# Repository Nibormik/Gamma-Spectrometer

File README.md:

# Gamma-Spectrometer
This is a Compact Gammaspectrometer Based On the Scematics and component choise of the [Open-Gamma-Detector](https://github.com/Open-Gamma-Project/Open-Gamma-Detector).
Its only Designed for testing purposes and should never be used in a production enviorment.  
<br>
This version of the Gamma spectrometer was designed with a few strict restrictions in mind.

#### Restrictions
<br>
The main rrestrictions:  <br>

- Power
    - <= 50ma
    - 5v
    - low noise
- physical limitations
    - pcb
        - width 50mm
        - height 30 mm
    - rocket interior diameter 98mm
        - max center height from pcb 38 mm
        - max edge height from pcb 28 mm 
- comunication
    - analog rocket input
        - update frequencey 2000hz - 4000hz
        - 8 bit resolution
    - digital input
        - 8bit digital paralell
        - estimated update frequency 20hz

## Similarities between projects

Since this is based upon the schematic of the Open Gamma Detector there are not allot of diffrences.  
Main diffrences are a diffrent cpu and the data output (wich is stricly analog)
Due to the enviorment, to-way comunictation is not possible so the bord does not support it.

The scintilator end general operational methon of the systen is equal to that of the Opgen Gamma Detector

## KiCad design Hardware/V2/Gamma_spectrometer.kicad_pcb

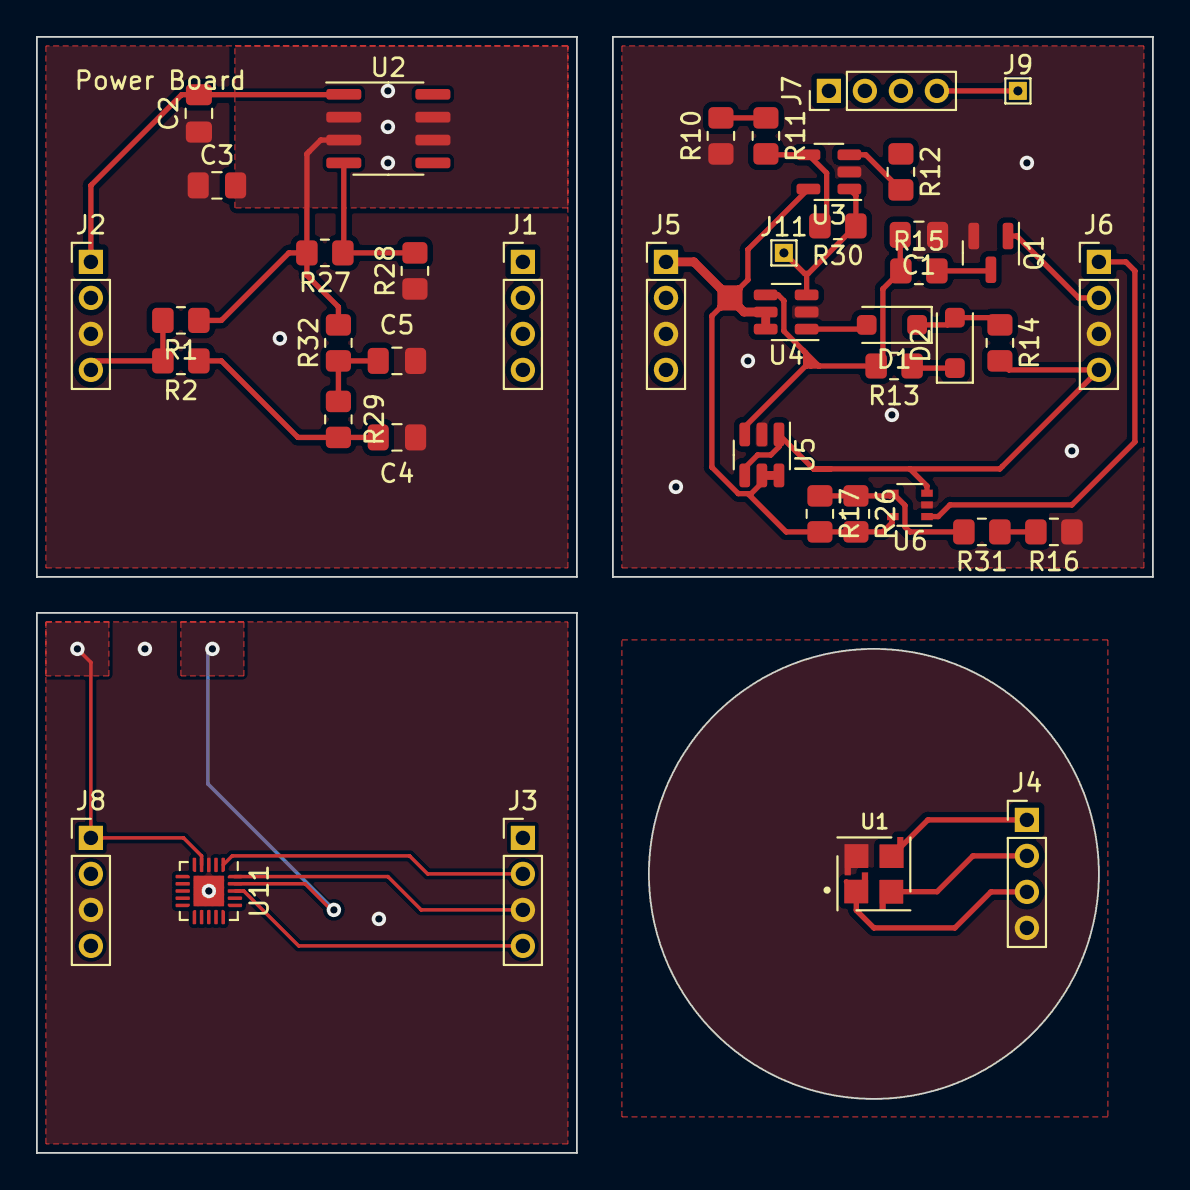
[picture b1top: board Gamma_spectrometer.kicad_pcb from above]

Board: 2 copper layers, 62.0 x 62.0 mm, 42 parts (0 on the bottom side), 32 nets.

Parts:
C1, C2, C3: C; C_0805_2012Metric_Pad1.18x1.45mm_HandSolder
C4, C5: 10n; C_0805_2012Metric_Pad1.18x1.45mm_HandSolder
D1, D2: PMEG6010CEH; D_SOD-123F
J1, J2, J3, J4, J5, J6, J7, J8: Conn_01x04; PinHeader_1x04_P2.00mm_Vertical
J9, J11: Test Pad; TestPoint_THTPad_1.0x1.0mm_Drill0.5mm
Q1: 2N7002; SOT-23
R1, R2: 0; R_0805_2012Metric_Pad1.20x1.40mm_HandSolder
R10, R11: 10; R_0805_2012Metric_Pad1.20x1.40mm_HandSolder
R12, R13, R29, R32: 49.9; R_0805_2012Metric_Pad1.20x1.40mm_HandSolder
R14, R15, R16: 1000; R_0805_2012Metric_Pad1.20x1.40mm_HandSolder
R17, R26: 107K; R_0805_2012Metric_Pad1.20x1.40mm_HandSolder
R27, R28, R30, R31: ?; R_0805_2012Metric_Pad1.20x1.40mm_HandSolder
U1: MICROFC-30035-SMT-TR1; XDCR_MICROFC-30035-SMT-TR1
U2: LM317L_SO8; SOIC-8_3.9x4.9mm_P1.27mm
U3: OPA356xxDBV; SOT-23-5
U4, U5: OPA357AIDVBR; SOT-23-6
U6: LMV7219M7; SOT-353_SC-70-5
U11: ATtiny1616-M; VQFN-20-1EP_3x3mm_P0.4mm_EP1.7x1.7mm

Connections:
+5V: J5.1, J8.1, R17.2, R26.2, U3.5 (V+), U4.5 (ENABLE), U4.6 (V+), U5.5 (ENABLE), U5.6 (V+), U6.5 (V+), U11.4 (VCC)
GND: C1.1, J5.3, J6.3, Q1.2 (S), R10.1, R16.1, U3.2 (V-), U4.2 (V-), U5.2 (V-), U6.2 (V-)
GND1: J4.4, U1.4
GND2: C2.1, C3.1, C4.2, C5.2, J2.3, R28.1
GND3: J3.3, J8.3, U11.3 (GND), U11.21 (GND)
INT: J6.1, U6.1
unnamed: C3.2, R1.1, R27.2, R32.2, U2.2 (VO), U2.3 (VO), U2.6 (VO), U2.7 (VO)
unnamed: C4.1, R2.1, R29.1
unnamed: C5.1, R29.2, R32.1
unnamed: D1.2 (A), U4.1
unnamed: D1.1 (K), D2.2 (A), R14.1
unnamed: D2.1 (K), R13.1
unnamed: C2.2, J2.1, U2.1 (VI)
unnamed: J2.4, R1.2, R2.2
unnamed: J3.1, U11.1 (PA2)
unnamed: J3.2, U11.20 (PA1)
unnamed: J3.4, U11.18 (PC3)
unnamed: J4.1, U1.3
unnamed: J4.2, U1.2
unnamed: J4.3, U1.1
unnamed: J11.1, R30.1, U3.1, U4.3 (+)
unnamed: Q1.3 (D), R15.2
unnamed: R10.2, R11.1
unnamed: R16.2, R31.1
unnamed: R27.1, R28.2, U2.4 (ADJ)
unnamed: R12.2, U3.3 (+)
unnamed: R11.2, R30.2, U3.4 (-)
unnamed: C1.2, R13.2, R15.1, U4.4 (-), U5.3 (+)
unnamed: R17.1, R26.1, R31.2, U6.4 (-)
Reset: J6.2, Q1.1 (G)
SIPM: J7.1, J7.2, J7.3, J7.4, J9.1, R12.1
Signal: J6.4, R14.2, U5.1, U5.4 (-), U6.3 (+)

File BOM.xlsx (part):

Column1 | Column2 | Column3 | Column4 | Column5 | Column6 | Column7 | Column8 | Column9 | Column10 | Column11
Source: | C:\Users\Nibne\Documents\Gamma Spectrometer\Hardware\Gamma_spectrometer.kicad_s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
Date: | 2/6/2023 2:52:58 PM
Tool: | Eeschema (6.0.8)
Generator: | C:\Program Files\KiCad\6.0\bin\scripting\plugins/bom_csv_grouped_by_value.py
Component Count: | 47
Individual Components:
Item | Qty | Reference(s) | Value | LibPart | Footprint | Datasheet | MANUFACTURER | MAXIMUM_PACKAGE_HEIGHT | PARTREV | STANDARD
 |  | C1 | C | Device:C | Capacitor_SMD:C_0805_2012Metric_Pad1.18x1.45mm_HandSolder | ~
 |  | C2 | C | Device:C | Capacitor_SMD:C_0805_2012Metric_Pad1.18x1.45mm_HandSolder | ~
 |  | C3 | C | Device:C | Capacitor_SMD:C_0805_2012Metric_Pad1.18x1.45mm_HandSolder | ~
 |  | C4 | 10n | Device:C | Capacitor_SMD:C_0805_2012Metric_Pad1.18x1.45mm_HandSolder | ~
 |  | C5 | 10n | Device:C | Capacitor_SMD:C_0805_2012Metric_Pad1.18x1.45mm_HandSolder | ~
 |  | D1 | PMEG6010CEH | Diode:PMEG6010CEH | Diode_SMD:D_SOD-123F | https://assets.nexperia.com/documents/data-sheet/PMEG6010CEH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
 |  | D2 | PMEG6010CEH | Diode:PMEG6010CEH | Diode_SMD:D_SOD-123F | https://assets.nexperia.com/documents/data-sheet/PMEG6010CEH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
 |  | J1 | Conn_01x04 | Connector_Generic:Conn_01x04 | Connector_PinHeader_2.00mm:PinHeader_1x04_P2.00mm_Vertical | ~
 |  | J2 | Conn_01x04 | Connector_Generic:Conn_01x04 | Connector_PinHeader_2.00mm:PinHeader_1x04_P2.00mm_Vertical | ~
 |  | J3 | Conn_01x01 | Connector_Generic:Conn_01x01 | Connector_PinHeader_2.00mm:PinHeader_1x01_P2.00mm_Vertical | ~
 |  | J4 | Conn_01x04 | Connector_Generic:Conn_01x04 | Connector_PinHeader_2.00mm:PinHeader_1x04_P2.00mm_Vertical | ~
 |  | J5 | Test Pad | Connector:Conn_01x01_Female | TestPoint:TestPoint_THTPad_1.0x1.0mm_Drill0.5mm | ~
 |  | J6 | Test Pad | Connector:Conn_01x01_Female | TestPoint:TestPoint_THTPad_1.0x1.0mm_Drill0.5mm | ~
 |  | J7 | Test Pad | Connector:Conn_01x01_Female | TestPoint:TestPoint_THTPad_1.0x1.0mm_Drill0.5mm | ~
 |  | J8 | Test Pad | Connector:Conn_01x01_Female | TestPoint:TestPoint_THTPad_1.0x1.0mm_Drill0.5mm | ~
 |  | J9 | Test Pad | Connector:Conn_01x01_Female | TestPoint:TestPoint_THTPad_1.0x1.0mm_Drill0.5mm | ~
 |  | J10 | Test Pad | Connector:Conn_01x01_Female | TestPoint:TestPoint_THTPad_1.0x1.0mm_Drill0.5mm | ~
 |  | J11 | Test Pad | Connector:Conn_01x01_Female | TestPoint:TestPoint_THTPad_1.0x1.0mm_Drill0.5mm | ~
 |  | J12 | Test Pad | Connector:Conn_01x01_Female | TestPoint:TestPoint_THTPad_1.0x1.0mm_Drill0.5mm | ~
 |  | Q1 | 2N7002 | Transistor_FET:2N7002 | Package_TO_SOT_SMD:SOT-23 | https://www.onsemi.com/pub/Collateral/NDS7002A-D.PDF
 |  | R1 | 49.9 | Device:R | Resistor_SMD:R_0805_2012Metric_Pad1.20x1.40mm_HandSolder | ~
 |  | R10 | 10 | Device:R | Resistor_SMD:R_0805_2012Metric_Pad1.20x1.40mm_HandSolder | ~
 |  | R11 | 10 | Device:R | Resistor_SMD:R_0805_2012Metric_Pad1.20x1.40mm_HandSolder | ~
 |  | R12 | 49.9 | Device:R | Resistor_SMD:R_0805_2012Metric_Pad1.20x1.40mm_HandSolder | ~
 |  | R13 | 49.9 | Device:R | Resistor_SMD:R_0805_2012Metric_Pad1.20x1.40mm_HandSolder | ~
 |  | R14 | 1000 | Device:R | Resistor_SMD:R_0805_2012Metric_Pad1.20x1.40mm_HandSolder | ~
 |  | R15 | 1000 | Device:R | Resistor_SMD:R_0805_2012Metric_Pad1.20x1.40mm_HandSolder | ~
 |  | R16 | 1000 | Device:R | Resistor_SMD:R_0805_2012Metric_Pad1.20x1.40mm_HandSolder | ~
 |  | R17 | 107K | Device:R | Resistor_SMD:R_0805_2012Metric_Pad1.20x1.40mm_HandSolder | ~
 |  | R26 | 107K | Device:R | Resistor_SMD:R_0805_2012Metric_Pad1.20x1.40mm_HandSolder | ~
 |  | R27 | ? | Device:R | Resistor_SMD:R_0805_2012Metric_Pad1.20x1.40mm_HandSolder | ~
 |  | R28 | ? | Device:R | Resistor_SMD:R_0805_2012Metric_Pad1.20x1.40mm_HandSolder | ~
 |  | R29 | 49.9 | Device:R | Resistor_SMD:R_0805_2012Metric_Pad1.20x1.40mm_HandSolder | ~
 |  | R30 | ? | Device:R | Resistor_SMD:R_0805_2012Metric_Pad1.20x1.40mm_HandSolder | ~
 |  | R31 | ? | Device:R | Resistor_SMD:R_0805_2012Metric_Pad1.20x1.40mm_HandSolder | ~
 |  | R32 | 49.9 | Device:R | Resistor_SMD:R_0805_2012Metric_Pad1.20x1.40mm_HandSolder | ~
 |  | R33 | 1000 | Device:R | Resistor_SMD:R_0805_2012Metric_Pad1.20x1.40mm_HandSolder | ~
 |  | R34 | 1000 | Device:R | Resistor_SMD:R_0805_2012Metric_Pad1.20x1.40mm_HandSolder | ~
 |  | SIPM1 | MICROFC-30035-SMT-TR1 | MICROFC-30035-SMT-TR1:MICROFC-30035-SMT-TR1 | MICROFC-30035-SMT-TR1:XDCR_MICROFC-30035-SMT-TR1 |  | On Semiconductor | 0.70 mm | Issue O | Manufacturer Recommendations
 |  | U2 | LM317L_SO8 | Regulator_Linear:LM317L_SO8 | Package_SO:SOIC-8_3.9x4.9mm_P1.27mm | http://www.ti.com/lit/ds/snvs775k/snvs775k.pdf
 |  | U3 | OPA356xxDBV | Amplifier_Operational:OPA356xxDBV | Package_TO_SOT_SMD:SOT-23-5 | http://www.ti.com/lit/ds/symlink/opa356.pdf
 |  | U4 | OPA357AIDVBR | Amplifier_Operational:OPA355NA | Package_TO_SOT_SMD:SOT-23-6 | http://www.ti.com/lit/ds/symlink/opa355.pdf
 |  | U5 | OPA357AIDVBR | Amplifier_Operational:OPA355NA | Package_TO_SOT_SMD:SOT-23-6 | http://www.ti.com/lit/ds/symlink/opa355.pdf
 |  | U6 | LMV7219M7 | Comparator:LMV7219M7 | Package_TO_SOT_SMD:SOT-353_SC-70-5 | https://www.ti.com/lit/ds/symlink/lmv7219.pdf
 |  | U7 | OPA356xxDBV | Amplifier_Operational:OPA356xxDBV | Package_TO_SOT_SMD:SOT-23-5 | http://www.ti.com/lit/ds/symlink/opa356.pdf
 |  | U8 | FODM217A | Isolator:FODM217A | Package_SO:SOP-4_4.4x2.6mm_P1.27mm | https://www.onsemi.com/pub/Collateral/FODM214-D.PDF
 |  | U11 | ATtiny1616-M | MCU_Microchip_ATtiny:ATtiny1616-M | Package_DFN_QFN:VQFN-20-1EP_3x3mm_P0.4mm_EP1.7x1.7mm | http://ww1.microchip.com/downloads/en/DeviceDoc/ATtiny3216_A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
Collated Components:
Item | Qty | Reference(s) | Value | LibPart | Footprint | Datasheet | MANUFACTURER | MAXIMUM_PACKAGE_HEIGHT | PARTREV | STANDARD
1 | 3 | C1, C2, C3 | C |  | Capacitor_SMD:C_0805_2012Metric_Pad1.18x1.45mm_HandSolder | ~
2 | 2 | C4, C5 | 10n |  | Capacitor_SMD:C_0805_2012Metric_Pad1.18x1.45mm_HandSolder | ~
3 | 2 | D1, D2 | PMEG6010CEH | Kan Erstates Med lignende Komponenter | Diode_SMD:D_SOD-123F | https://assets.nexperia.com/documents/data-sheet/PMEG6010CEH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
4 | 3 | J1, J2, J4 | Conn_01x04 | 1stk Rakett konnector 2stk pin header | Connector_PinHeader_2.00mm:PinHeader_1x04_P2.00mm_Vertical | ~
5 | 1 | J3 | Conn_01x01 | rakett CLK konnector | Connector_PinHeader_2.00mm:PinHeader_1x01_P2.00mm_Vertical | ~
6 | 8 | J5, J6, J7, J8, J9, J10, J11, J12 | Test Pad |  | TestPoint:TestPoint_THTPad_1.0x1.0mm_Drill0.5mm | ~
7 | 1 | Q1 | 2N7002 | Kan Erstates Med lignende Komponenter | Package_TO_SOT_SMD:SOT-23 | https://www.onsemi.com/pub/Collateral/NDS7002A-D.PDF
8 | 5 | R1, R12, R13, R29, R32 | 49.9 |  | Resistor_SMD:R_0805_2012Metric_Pad1.20x1.40mm_HandSolder | ~
9 | 2 | R10, R11 | 10 |  | Resistor_SMD:R_0805_2012Metric_Pad1.20x1.40mm_HandSolder | ~
10 | 5 | R14, R15, R16, R33, R34 | 1000 |  | Resistor_SMD:R_0805_2012Metric_Pad1.20x1.40mm_HandSolder | ~
11 | 2 | R17, R26 | 107K |  | Resistor_SMD:R_0805_2012Metric_Pad1.20x1.40mm_HandSolder | ~
12 | 4 | R27, R28, R30, R31 | ? | må testes for og finne verdi | Resistor_SMD:R_0805_2012Metric_Pad1.20x1.40mm_HandSolder | ~
13 | 1 | SIPM1 | MICROFC-30035-SMT-TR1 |  | MICROFC-30035-SMT-TR1:XDCR_MICROFC-30035-SMT-TR1 |  | On Semiconductor | 0.70 mm | Issue O | Manufacturer Recommendations
14 | 1 | U2 | LM317L_SO8 | Regulator_Linear:LM317L_SO8 | Package_SO:SOIC-8_3.9x4.9mm_P1.27mm | http://www.ti.com/lit/ds/snvs775k/snvs775k.pdf
15 | 2 | U3, U7 | OPA356AIDBVR | Amplifier_Operational:OPA356xxDBVR | Package_TO_SOT_SMD:SOT-23-5 | http://www.ti.com/lit/ds/symlink/opa356.pdf
16 | 2 | U4, U5 | OPA357AIDBVR | Amplifier_Operational:OPA357xxDBVR | Package_TO_SOT_SMD:SOT-23-6 | http://www.ti.com/lit/ds/symlink/opa355.pdf
17 | 1 | U6 | LMV7219M7 | Comparator:LMV7219M7 | Package_TO_SOT_SMD:SOT-353_SC-70-5 | https://www.ti.com/lit/ds/symlink/lmv7219.pdf
18 | 1 | U8 | FODM217A | Kan Erstates Med lignende Komponenter | Package_SO:SOP-4_4.4x2.6mm_P1.27mm | https://www.onsemi.com/pub/Collateral/FODM214-D.PDF
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
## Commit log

2023-01-13 Create LICENSE
2023-01-13 BOM scv update
2023-01-13 README Update
2023-01-13 some stuff
2023-01-13 stuff again
2023-01-13 code stuff i guess
2023-02-06 stuff
2023-02-19 bacup file
2023-03-09 fixed som BOM stuff
2023-06-09 Reworked entre board to be modular now more practical to use outside of the very limited desig limitations originally planed
2023-06-09 some more modular stuff
